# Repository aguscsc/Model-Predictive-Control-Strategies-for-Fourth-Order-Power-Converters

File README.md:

# Model-Predictive-Control-Strategies-for-Fourth-Order-Power-Converters
This repository contains the design an implementation of a SEPIC (Single-Ended Primary-Inductor Converter) to test and compare the application of model predictive control on fourth-order power converters.

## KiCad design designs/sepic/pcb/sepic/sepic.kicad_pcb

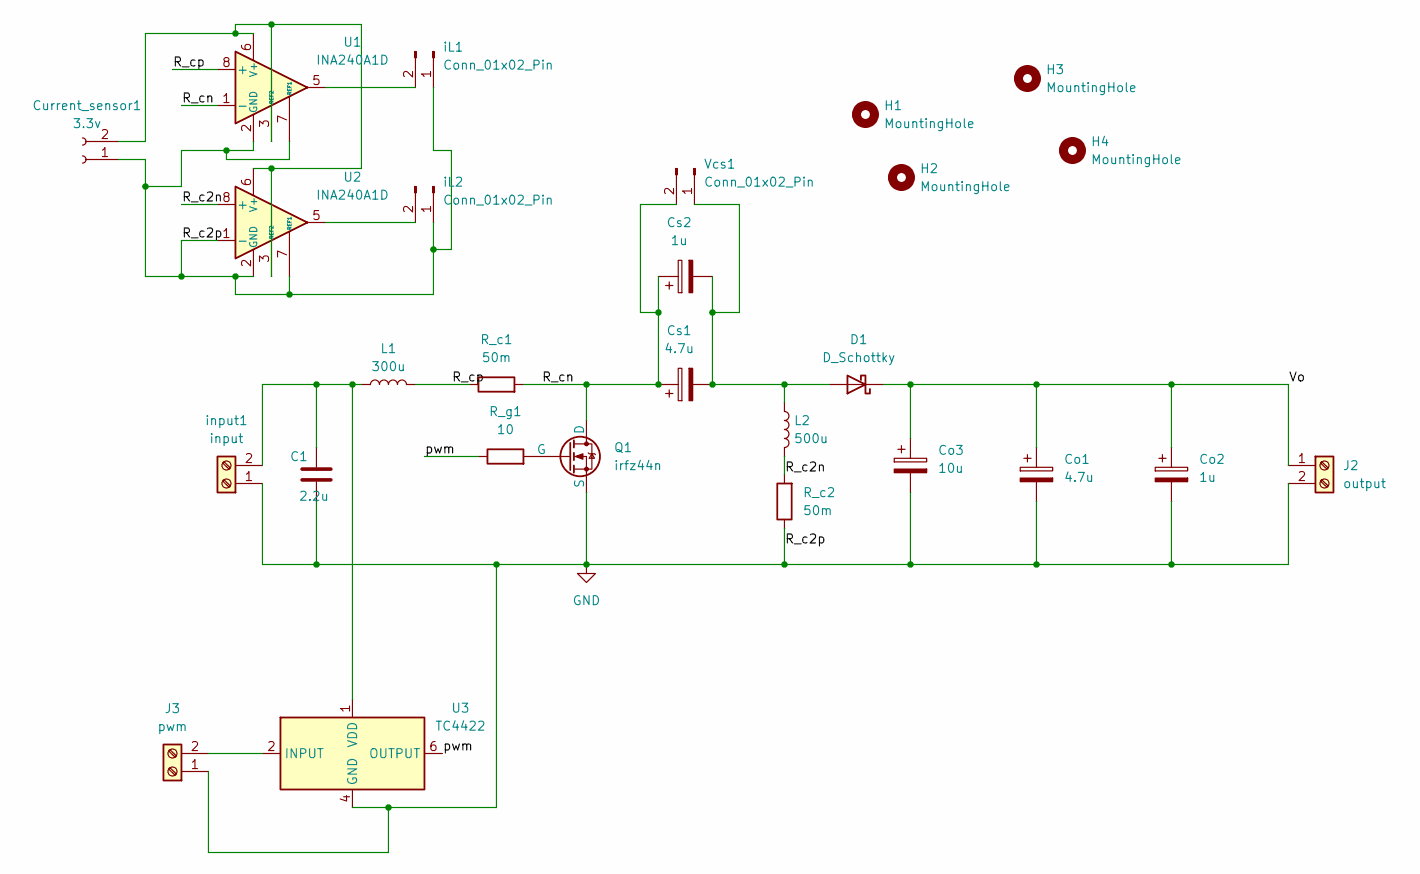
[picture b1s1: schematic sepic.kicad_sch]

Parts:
C1: 2.2u; C_Disc_D5.0mm_W2.5mm_P2.50mm
Co1: 4.7u; CP_Radial_D4.0mm_P2.00mm
Co2: 1u; CP_Radial_D4.0mm_P2.00mm
Co3: 10u; CP_Radial_D4.0mm_P2.00mm
Cs1: 4.7u; CP_Radial_D4.0mm_P2.00mm
Cs2: 1u; CP_Radial_D4.0mm_P2.00mm
Current_sensor1: 3.3v; PinSocket_1x02_P2.54mm_Vertical
D1: D_Schottky; D_DO-201AE_P15.24mm_Horizontal
H1, H2, H3, H4: MountingHole; MountingHole_3.2mm_M3_DIN965
J2: output; TerminalBlock_Phoenix_MKDS-1,5-2-5.08_1x02_P5.08mm_Horizont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
J3: pwm; TerminalBlock_Phoenix_MKDS-1,5-2-5.08_1x02_P5.08mm_Horizont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
L1: 300u; inductor_20x7.5
L2: 500u; inductor_20x7.5
Q1: irfz44n; TO-220-3_Vertical
R_c1: 50m; R_Axial_DIN0414_L11.9mm_D4.5mm_P15.24mm_Horizontal
R_c2: 50m; R_Axial_DIN0414_L11.9mm_D4.5mm_P5.08mm_Vertical
R_g1: 10; R_Axial_DIN0207_L6.3mm_D2.5mm_P10.16mm_Horizontal
U1, U2: INA240A1D; SOIC-8_3.9x4.9mm_P1.27mm
U3: TC4422; DIP-8_W7.62mm
Vcs1: Conn_01x02_Pin; PinHeader_1x02_P2.54mm_Vertical
iL1, iL2: Conn_01x02_Pin; PinHeader_1x02_P2.54mm_Vertical
input1: input; TerminalBlock_Phoenix_MKDS-1,5-2-5.08_1x02_P5.08mm_Horizont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

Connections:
/R_c2n: L2.2, R_c2.2, U2.8 (+)
/R_cn: Cs1.1, Cs2.1, Q1.2 (D), R_c1.2, U1.1 (-), Vcs1.2
/R_cp: L1.2, R_c1.1, U1.8 (+)
/Vo: Co1.1, Co2.1, Co3.1, D1.1 (K), J2.1
/pwm: R_g1.1, U3.6 (OUTPUT), U3.7 (OUTPUT)
GND: C1.2, Co1.2, Co2.2, Co3.2, Current_sensor1.1, J2.2, J3.1, Q1.3 (S), R_c2.1, U1.2 (GND), U1.4 (GND), U1.7 (REF1), U2.1 (-), U2.2 (GND), U2.4 (GND), U2.7 (REF1), U3.4 (GND), U3.5 (GND), iL1.1, iL2.1, input1.1
unnamed: Current_sensor1.2, U1.3 (REF2), U1.6 (V+), U2.3 (REF2), U2.6 (V+)
unnamed: Cs1.2, Cs2.2, D1.2 (A), L2.1, Vcs1.1
unnamed: J3.2, U3.2 (INPUT)
unnamed: Q1.1 (G), R_g1.2
unnamed: U1.5, iL1.2
unnamed: U2.5, iL2.2
unnamed: C1.1, L1.1, U3.1 (VDD), U3.8 (VDD), input1.2

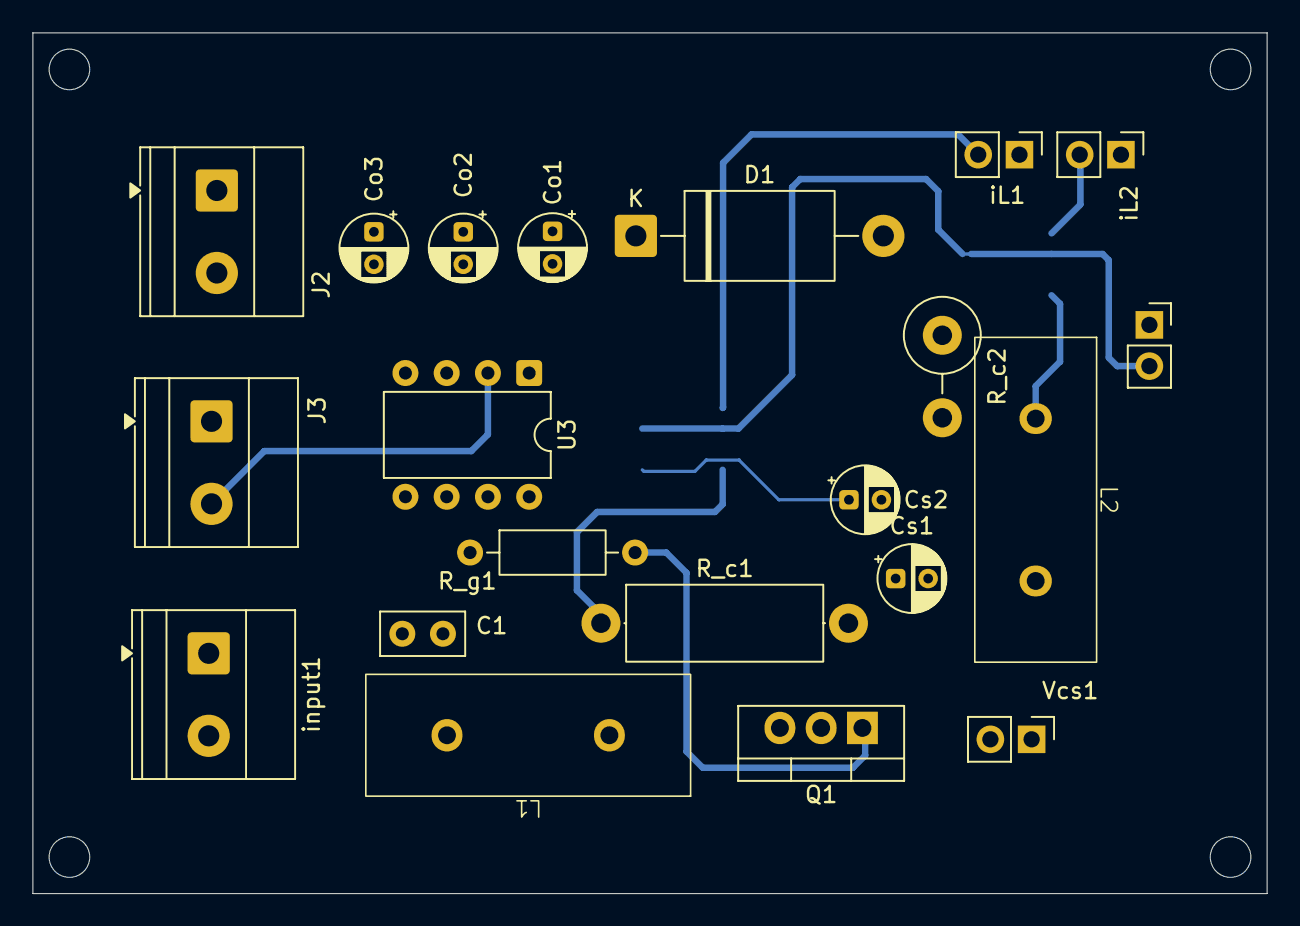
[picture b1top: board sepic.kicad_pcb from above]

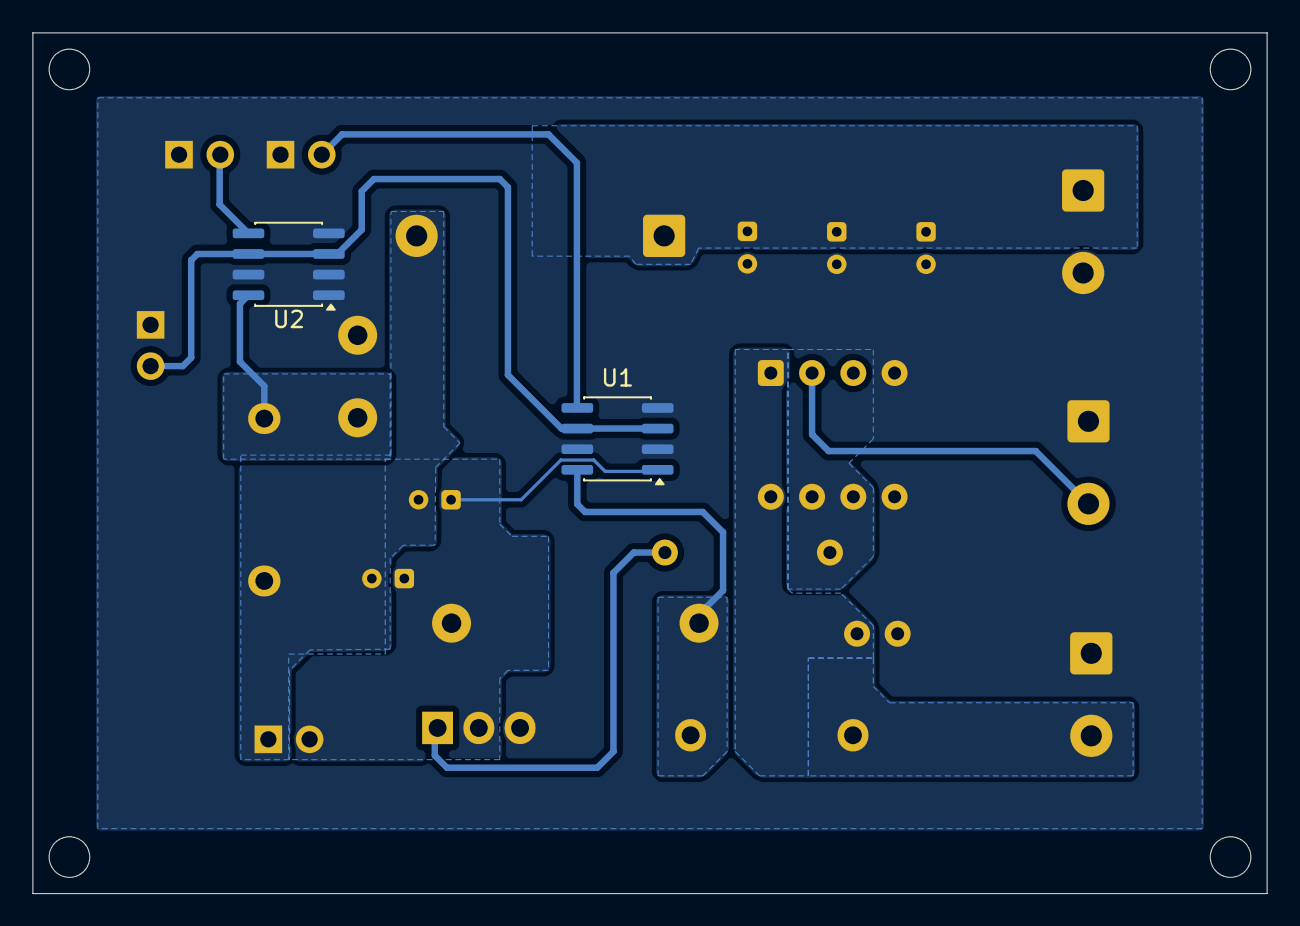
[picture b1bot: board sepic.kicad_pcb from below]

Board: 2 copper layers, 76.0 x 53.0 mm, 27 parts (2 on the bottom side), 13 nets.
